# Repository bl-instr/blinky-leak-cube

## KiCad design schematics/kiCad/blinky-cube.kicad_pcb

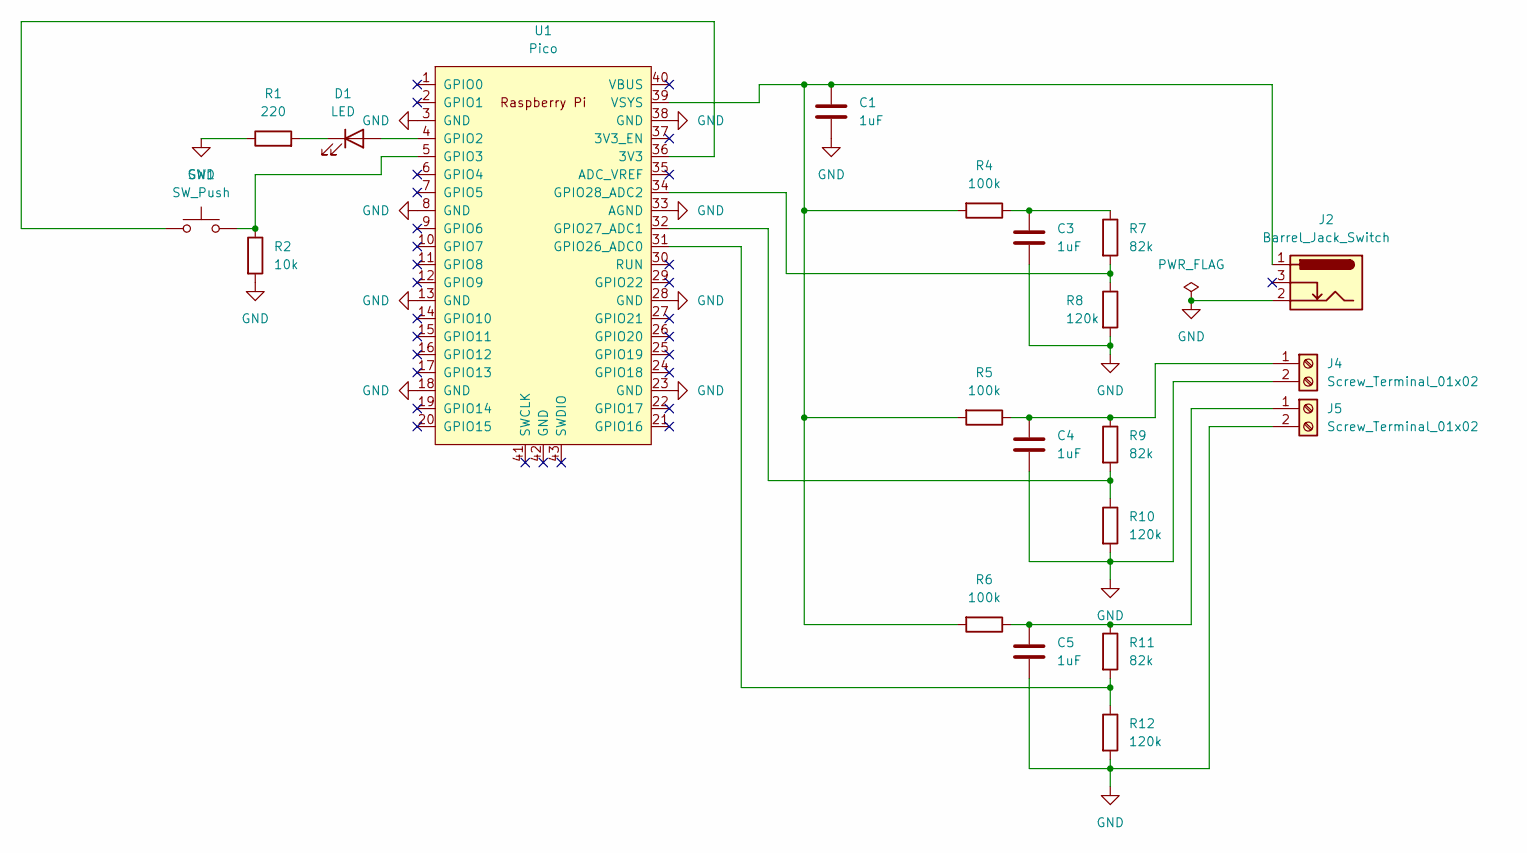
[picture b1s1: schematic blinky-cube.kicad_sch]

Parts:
C1, C3, C4, C5: 1uF; C_Disc_D4.7mm_W2.5mm_P5.00mm
D1: LED; LED_D5.0mm
J2: Barrel_Jack_Switch; BarrelJack_Horizontal
J4, J5: Screw_Terminal_01x02; TerminalBlock_Phoenix_MKDS-3-2-5.08_1x02_P5.08mm_Horizontal
R1: 220; R_Axial_DIN0207_L6.3mm_D2.5mm_P7.62mm_Horizontal
R2: 10k; R_Axial_DIN0207_L6.3mm_D2.5mm_P7.62mm_Horizontal
R4, R5, R6: 100k; R_Axial_DIN0207_L6.3mm_D2.5mm_P7.62mm_Horizontal
R7, R9, R11: 82k; R_Axial_DIN0207_L6.3mm_D2.5mm_P7.62mm_Horizontal
R8, R10, R12: 120k; R_Axial_DIN0207_L6.3mm_D2.5mm_P7.62mm_Horizontal
SW1: SW_Push; SW_PUSH_6mm
U1: Pico; RPi_Pico_SMD_TH

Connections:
GND: C1.2, C3.2, C4.2, C5.2, J2.2, J4.2, J5.2, R1.1, R2.2, R8.2, R10.2, R12.2, U1.3 (GND), U1.8 (GND), U1.13 (GND), U1.18 (GND), U1.23 (GND), U1.28 (GND), U1.33 (AGND), U1.38 (GND)
unnamed: C3.1, R4.1, R7.1
unnamed: D1.2 (A), U1.4 (GPIO2)
unnamed: D1.1 (K), R1.2
unnamed: C4.1, J4.1, R5.1, R9.1
unnamed: C5.1, J5.1, R6.1, R11.1
unnamed: SW1.1, U1.36 (3V3)
unnamed: R2.1, SW1.2, U1.5 (GPIO3)
unnamed: R11.2, R12.1, U1.31 (GPIO26_ADC0)
unnamed: R9.2, R10.1, U1.32 (GPIO27_ADC1)
unnamed: R7.2, R8.1, U1.34 (GPIO28_ADC2)
unnamed: C1.1, J2.1, R4.2, R5.2, R6.2, U1.39 (VSYS)

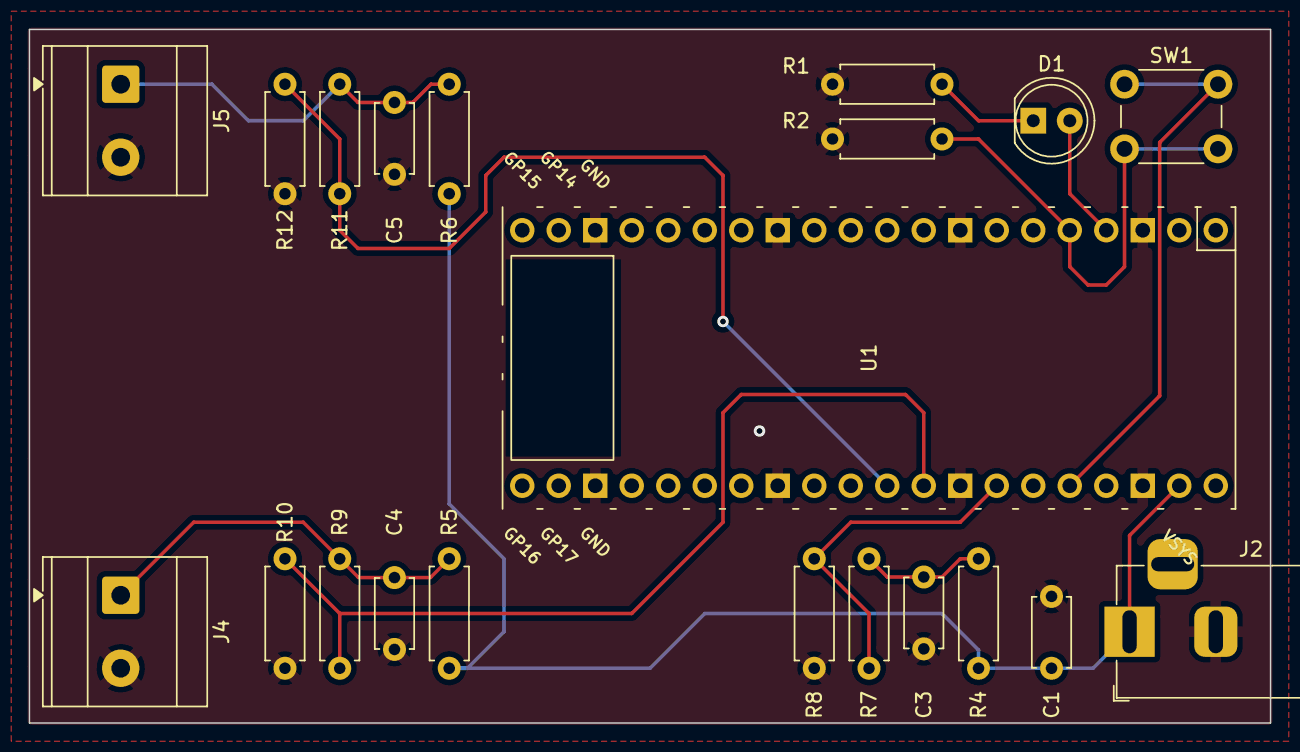
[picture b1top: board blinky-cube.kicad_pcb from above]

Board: 2 copper layers, 86.4 x 48.3 mm, 21 parts (0 on the bottom side), 12 nets.

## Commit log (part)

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2023-09-05 with battery holder design
2023-11-21 before switch back to cplusplus
2023-11-21 just publishing no reading
2023-12-02 added print diagnostic flag
2023-12-05 added readme
2023-12-05 updated read me
2024-02-22 added bom
2024-03-03 added wifi reboot after too may attempts
2024-04-17 changed ot one-core
2024-10-22 update kicad
2024-10-28 added check to web server that it is requesting web page
2025-02-14 working with picoW
